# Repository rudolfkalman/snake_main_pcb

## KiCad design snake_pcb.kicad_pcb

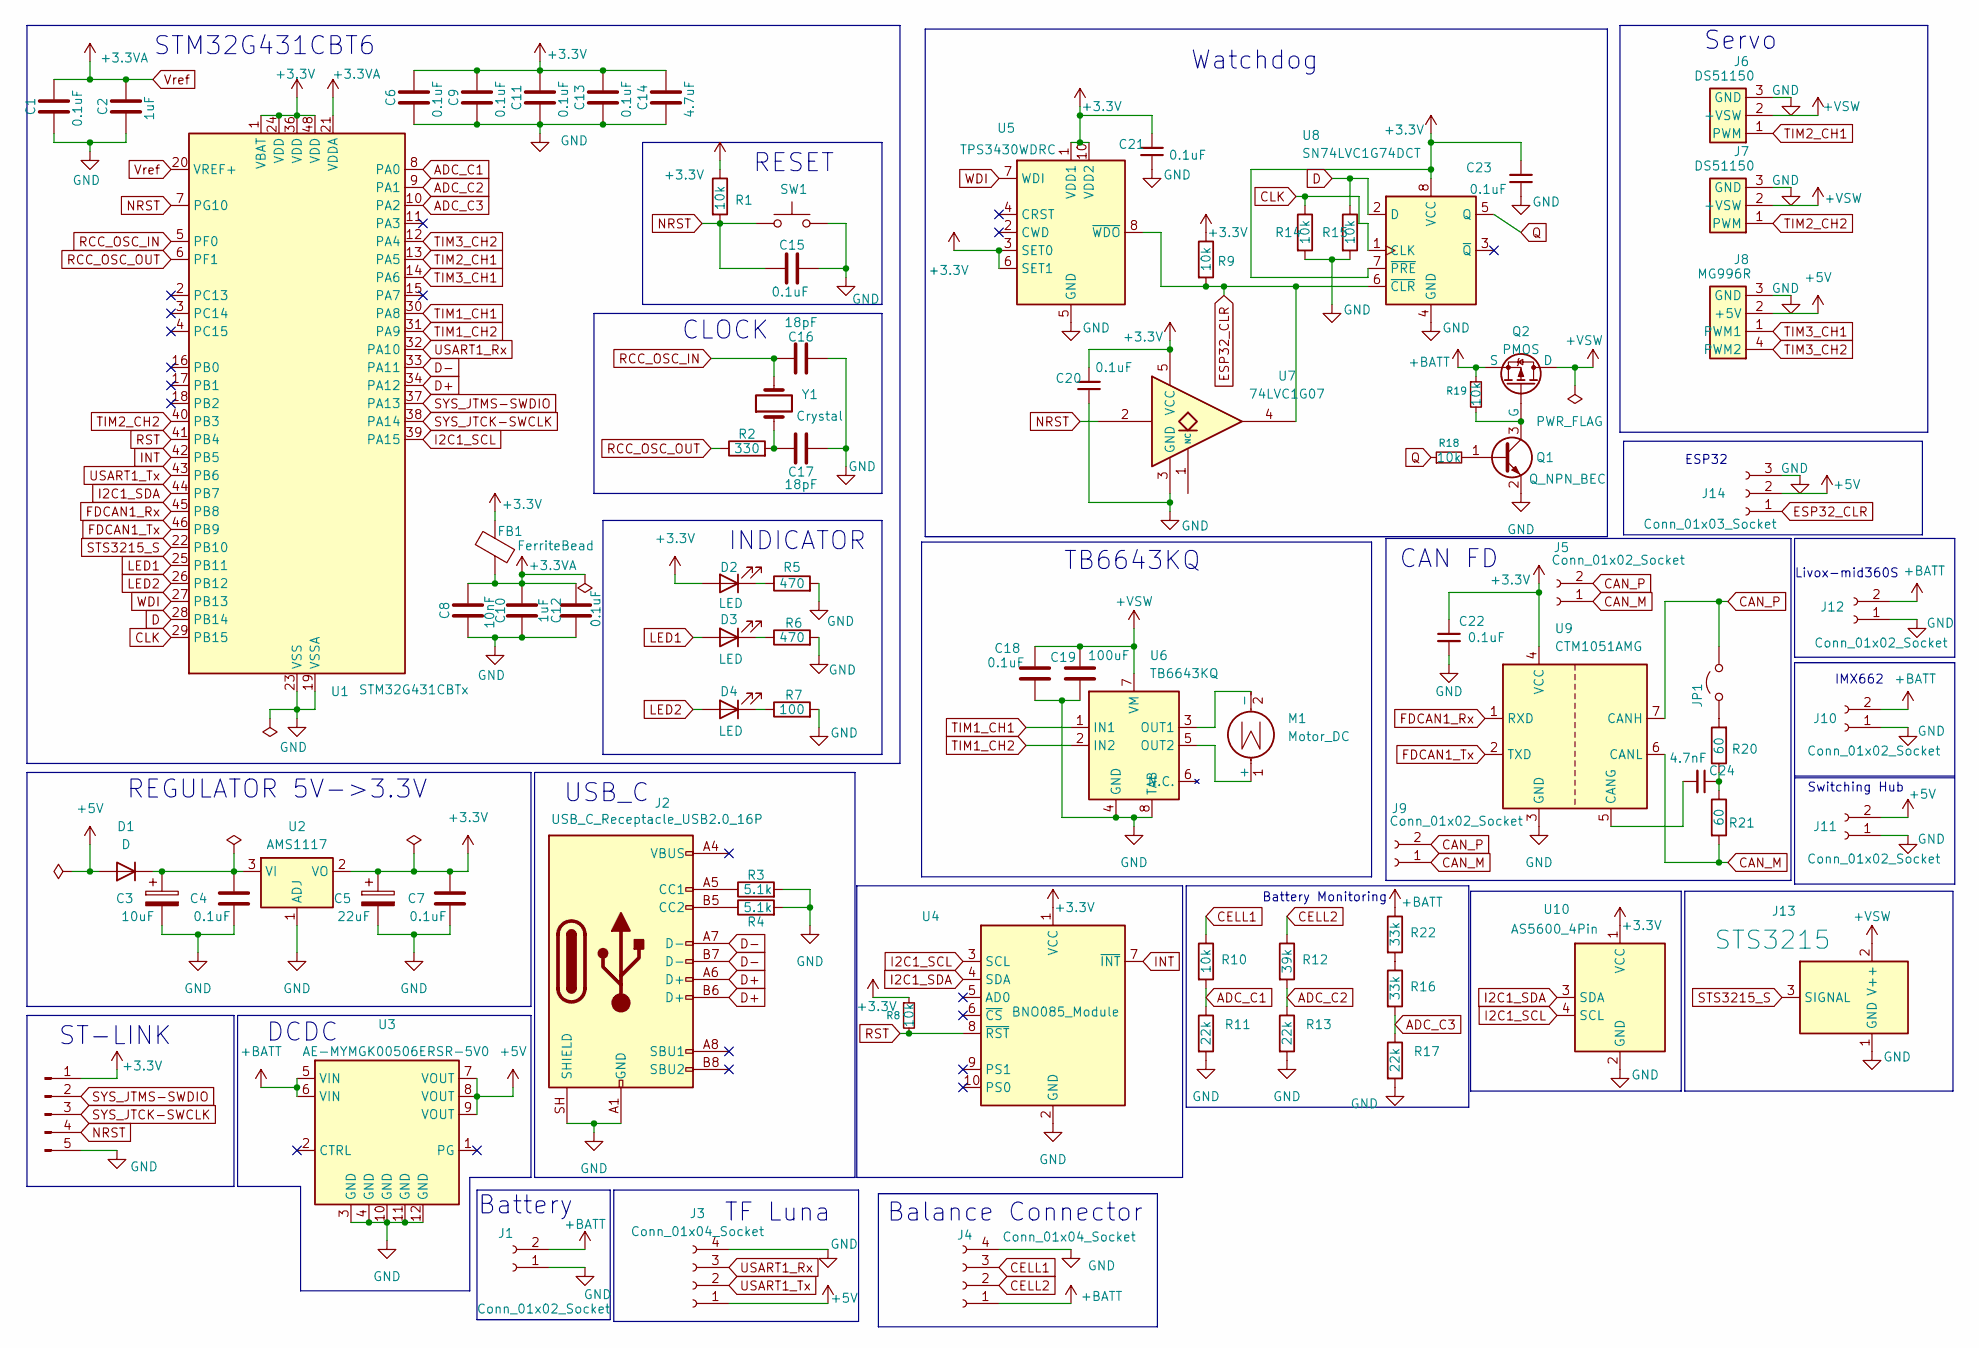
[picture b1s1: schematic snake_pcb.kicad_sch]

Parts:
C1, C4, C6, C7, C9, C11, C12, C13, C15, C18, C20, C21, C22, C23: 0.1uF; C_0603_1608Metric
C2, C10: 1uF; C_0603_1608Metric
C3: 10uF; C_CASE-A-3216-18(mm)
C5: 22uF; C_CASE-A-3216-18(mm)
C8: 10nF; C_0603_1608Metric
C14: 4.7uF; C_0603_1608Metric
C16, C17: 18pF; C_0603_1608Metric
C19: 100uF; C_Elec_6.3x7.7
C24: 4.7nF; C_0603_1608Metric
D1: D; D_DO-214AC(SMA)
D2, D3, D4: LED; LED_0603_1608Metric
FB1: FerriteBead; L_0603_1608Metric
J1: Conn_01x02_Socket; AMASS_XT30PW-M_1x02_P2.50mm_Horizontal
J2: USB_C_Receptacle_USB2.0_16P; USB_C_Receptacle_GCT_USB4110
J3: Conn_01x04_Socket; PinHeader_1x04_P2.54mm_Vertical
J4: Conn_01x04_Socket; JST_XH_B4B-XH-A_1x04_P2.50mm_Vertical
J5: Conn_01x02_Socket; JST_XH_S2B-XH-A_1x02_P2.50mm_Horizontal
J6, J7: DS51150; Servo_3Wire_3x6mm_P5mm
J8: MG996R; Servo_4Wire_3x6mm_P5mm
J9, J11: Conn_01x02_Socket; JST_XH_B2B-XH-A_1x02_P2.50mm_Vertical
J10: Conn_01x02_Socket; JST_PH_B2B-PH-K_1x02_P2.00mm_Vertical
J12: Conn_01x02_Socket; AMASS_XT30PW-F_1x02_P2.50mm_Horizontal
J13: STS3215; Molex_SPOX_5267-03A_1x03_P2.50mm_Vertical
J14: Conn_01x03_Socket; PinHeader_1x03_P2.54mm_Vertical
JP1: Jumper_2_Open; R_0603_1608Metric
M1: Motor_DC; AMASS_XT30PW-F_1x02_P2.50mm_Horizontal
Q1: Q_NPN_BEC; SOT-23
Q2: PMOS; TO-252-2_TabPin1
R1, R8, R9, R10, R14, R15, R18, R19: 10k; R_0603_1608Metric
R2: 330; R_0603_1608Metric
R3, R4: 5.1k; R_0603_1608Metric
R5, R6: 470; R_0603_1608Metric
R7: 100; R_0603_1608Metric
R11, R13, R17: 22k; R_0603_1608Metric
R12: 39k; R_0805_2012Metric
R16, R22: 33k; R_0603_1608Metric
R20, R21: 60; R_0603_1608Metric
ST-LINK1: Conn_01x05_Pin; PinHeader_1x05_P2.54mm_Vertical
SW1: SW_Push; SW_Tactile_SPST_NO_Straight_CK_PTS636Sx25SMTRLFS
U1: STM32G431CBTx; LQFP-48_7x7mm_P0.5mm
U2: AMS1117; SOT-223-3_TabPin2
U3: AE-MYMGK00506ERSR-5V0
U4: BNO085_Module; BNO085_Module_25.8x15.5mm_1x10_P2.54mm
U5: TPS3430WDRC; VSON-10-1EP_3x3mm_P0.5mm_EP1.65x2.4mm
U6: TB6643KQ; TB6643KQ_HSIP7_PCBHeatsink
U7: 74LVC1G07; SOT-353_SC-70-5
U8: SN74LVC1G74DCT; SSOP-8_2.95x2.8mm_P0.65mm
U9: CTM1051AMG; ZLG_CTM1051AMG_12.8x10.2mm_P2.54mm
U10: AS5600_4Pin; PinHeader_1x04_P2.54mm_Vertical
Y1: Crystal; Crystal_SMD_3225-4Pin_3.2x2.5mm

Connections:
+3.3V: C5.1, C6.2, C7.1, C9.2, C11.2, C13.2, C14.2, C20.1, C21.1, C22.1, C23.1, D2.2 (A), FB1.1, R1.1, R8.1, R9.1, ST-LINK1.1, U1.1 (VBAT), U1.24 (VDD), U1.36 (VDD), U1.48 (VDD), U2.2 (VO), U4.1 (VCC), U5.1 (VDD1), U5.3 (SET0), U5.6 (SET1), U5.10 (VDD2), U7.5 (VCC), U8.7 (~PRE), U8.8 (VCC), U9.4 (VCC), U10.1 (VCC)
+5V: D1.2 (A), J3.1, J8.2 (+5V), J11.2, J14.2, U3.7 (VOUT), U3.8 (VOUT), U3.9 (VOUT)
+BATT: J1.2, J4.1, J10.2, J12.2, Q2.3 (S), R19.1, R22.1, U3.5 (VIN), U3.6 (VIN)
+VSW: C18.1, C19.1, J6.2 (+VSW), J7.2 (+VSW), J13.2 (V++), Q2.1 (D), U6.7 (VM)
ADC_C1: R10.2, R11.1, U1.8 (PA0)
ADC_C2: R12.2, R13.1, U1.9 (PA1)
ADC_C3: R16.2, R17.1, U1.10 (PA2)
CAN_M: J5.1, J9.1, R21.2, U9.6 (CANL)
CAN_P: J5.2, J9.2, JP1.2 (B), U9.7 (CANH)
CELL1: J4.3, R10.1
CELL2: J4.2, R12.1
CLK: R14.1, U1.29 (PB15), U8.1 (CLK)
D: R15.1, U1.28 (PB14), U8.2 (D)
D+: J2.A6 (D+), J2.B6 (D+), U1.34 (PA12)
D-: J2.A7 (D-), J2.B7 (D-), U1.33 (PA11)
ESP32_CLR: J14.1, R9.2, U5.8 (~WDO), U7.4, U8.6 (~CLR)
FDCAN1_Rx: U1.45 (PB8), U9.1 (RXD)
FDCAN1_Tx: U1.46 (PB9), U9.2 (TXD)
GND: C1.1, C2.1, C3.2, C4.2, C5.2, C6.1, C7.2, C8.1, C9.1, C10.1, C11.1, C12.1, C13.1, C14.1, C15.2, C16.2, C17.1, C18.2, C19.2, C20.2, C21.2, C22.2, C23.2, J1.1, J2.A1 (GND), J2.A12 (GND), J2.B1 (GND), J2.B12 (GND), J2.SH (SHIELD), J3.4, J4.4, J6.3 (GND), J7.3 (GND), J8.3 (GND), J10.1, J11.1, J12.1, J13.1 (GND), J14.3, Q1.2 (E), R3.2, R4.2, R5.2, R6.2, R7.2, R11.2, R13.2, R14.2, R15.2, R17.2, ST-LINK1.5, SW1.2, U1.19 (VSSA), U1.23 (VSS), U1.35 (VSS), U1.47 (VSS), U2.1 (ADJ), U3.3 (GND), U3.4 (GND), U3.10 (GND), U3.11 (GND), U3.12 (GND), U4.2 (GND), U5.5 (GND), U5.11 (GND), U6.4 (GND), U6.8 (TAB), U7.3 (GND), U8.4 (GND), U9.3 (GND), U10.2 (GND)
I2C1_SCL: U1.39 (PA15), U4.3 (SCL), U10.4 (SCL)
I2C1_SDA: U1.44 (PB7), U4.4 (SDA), U10.3 (SDA)
INT: U1.42 (PB5), U4.7 (~INT)
LED1: D3.2 (A), U1.25 (PB11)
LED2: D4.2 (A), U1.26 (PB12)
NRST: C15.1, R1.2, ST-LINK1.4, SW1.1, U1.7 (PG10), U7.2
unnamed: C17.2, R2.2, Y1.1
unnamed: C24.1, R20.1, R21.1
unnamed: C3.1, C4.1, D1.1 (K), U2.3 (VI)
unnamed: D2.1 (K), R5.1
unnamed: D3.1 (K), R6.1
unnamed: D4.1 (K), R7.1
unnamed: J2.A5 (CC1), R3.1
unnamed: J2.B5 (CC2), R4.1
unnamed: JP1.1 (A), R20.2
unnamed: M1.1 (+), U6.5 (OUT2)
unnamed: M1.2 (-), U6.3 (OUT1)
unnamed: Q1.1 (B), R18.2
unnamed: Q1.3 (C), Q2.2 (G), R19.2
unnamed: R16.1, R22.2
unnamed: C24.2, U9.5 (CANG)
Q: R18.1, U8.5 (Q)
RCC_OSC_IN: C16.1, U1.5 (PF0), Y1.2
RCC_OSC_OUT: R2.1, U1.6 (PF1)
RST: R8.2, U1.41 (PB4), U4.8 (~RST)
STS3215_S: J13.3 (SIGNAL), U1.22 (PB10)
SYS_JTCK-SWCLK: ST-LINK1.3, U1.38 (PA14)
SYS_JTMS-SWDIO: ST-LINK1.2, U1.37 (PA13)
TIM1_CH1: U1.30 (PA8), U6.1 (IN1)
TIM1_CH2: U1.31 (PA9), U6.2 (IN2)
TIM2_CH1: J6.1 (PWM), U1.13 (PA5)
TIM2_CH2: J7.1 (PWM), U1.40 (PB3)
TIM3_CH1: J8.1 (PWM1), U1.14 (PA6)
TIM3_CH2: J8.4 (PWM2), U1.12 (PA4)
USART1_Rx: J3.3, U1.32 (PA10)
USART1_Tx: J3.2, U1.43 (PB6)
Vref: C1.2, C2.2, C8.2, C10.2, C12.2, FB1.2, U1.20 (VREF+), U1.21 (VDDA)
WDI: U1.27 (PB13), U5.7 (WDI)

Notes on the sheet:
STM32G431CBT6
INDICATOR
DCDC
Battery
Battery Monitoring
CAN FD
ST-LINK
USB_C
Balance Connector
Livox-mid360S
REGULATOR 5V->3.3V
TF Luna
Servo
Switching Hub
CLOCK
TB6643KQ
ESP32
IMX662
RESET
Watchdog

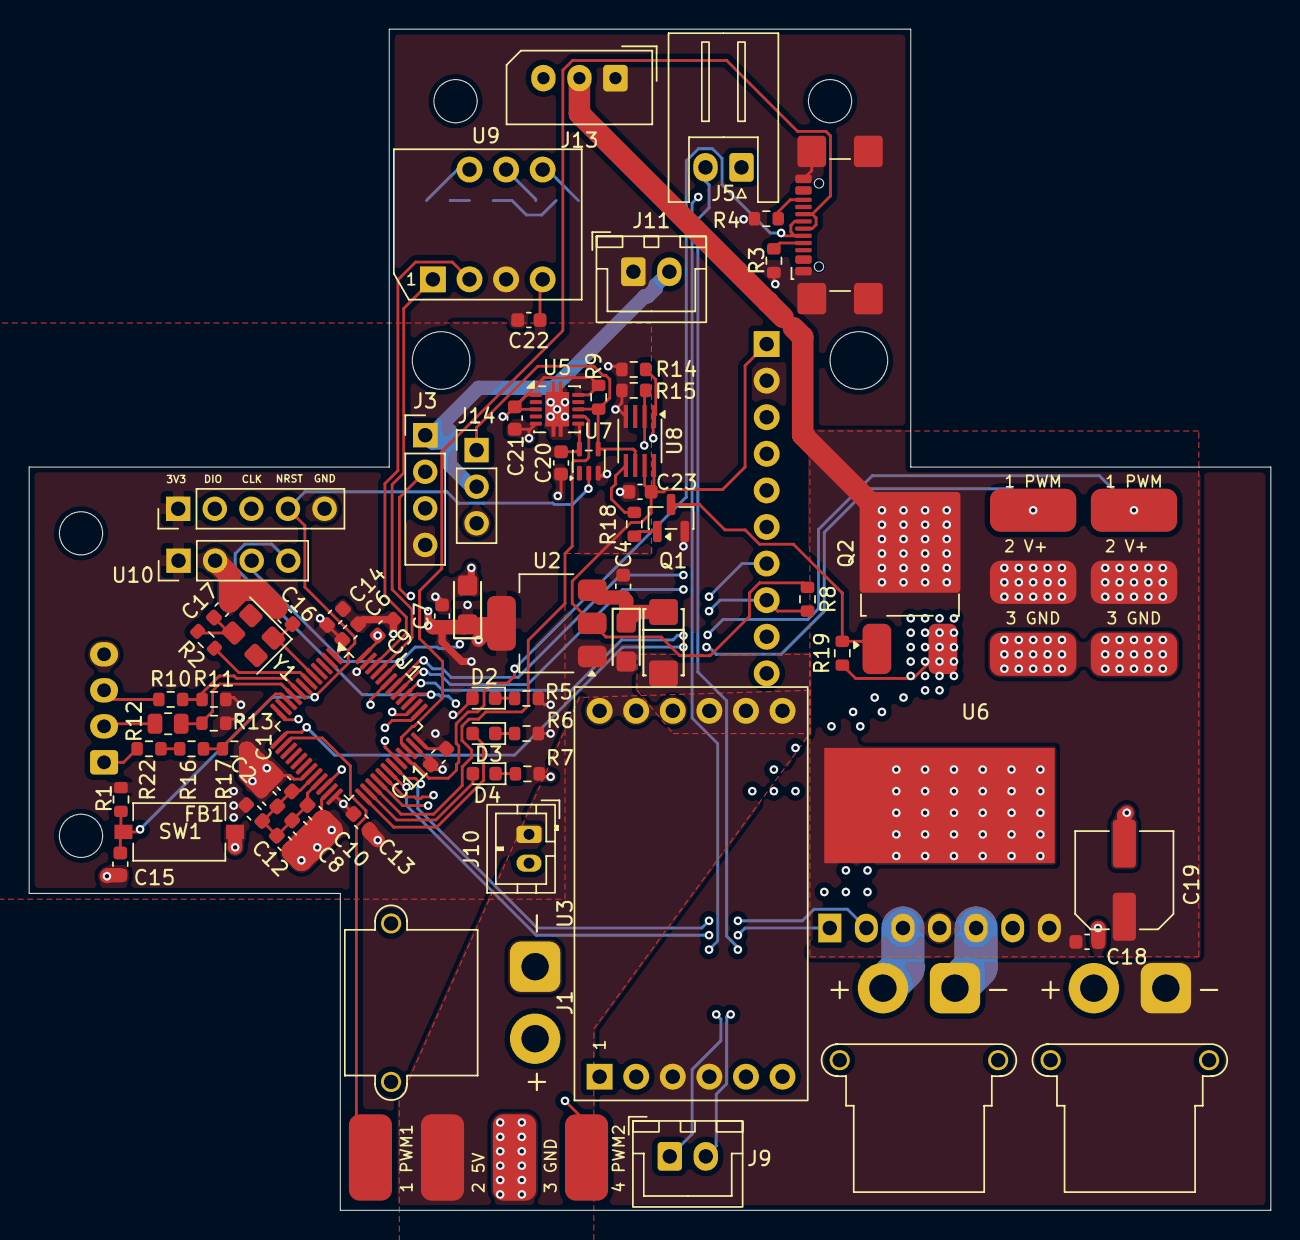
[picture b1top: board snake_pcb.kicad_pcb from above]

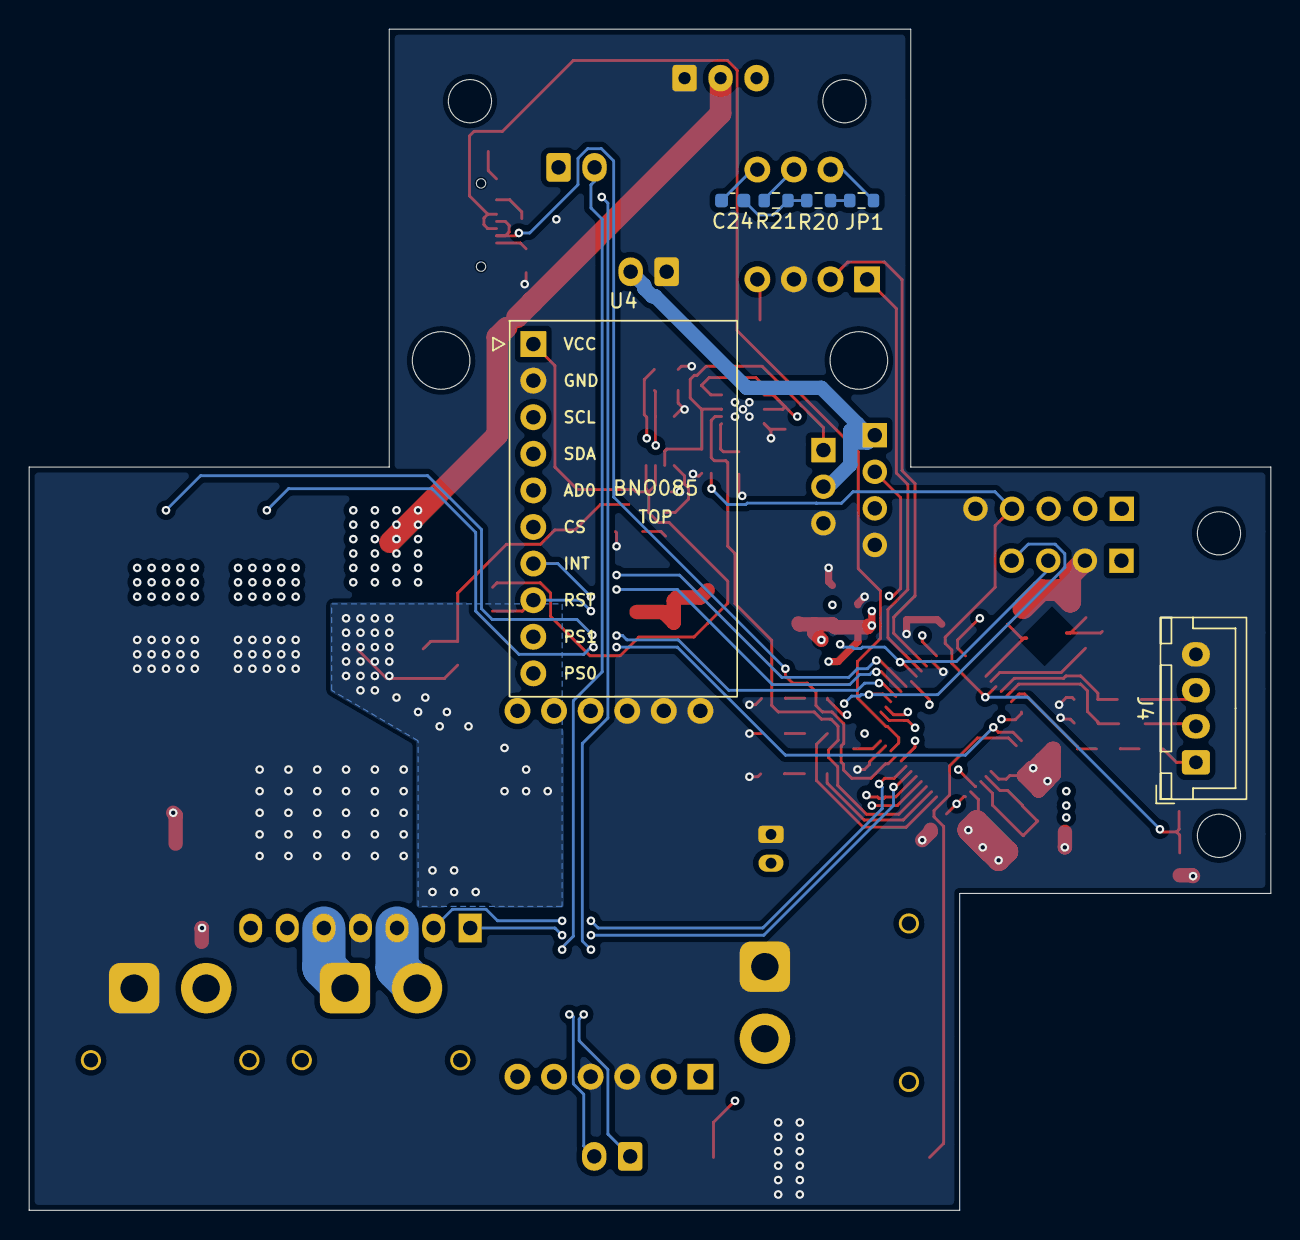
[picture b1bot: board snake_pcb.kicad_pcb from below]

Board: 4 copper layers, 86.2 x 82.0 mm, 82 parts (6 on the bottom side), 57 nets.

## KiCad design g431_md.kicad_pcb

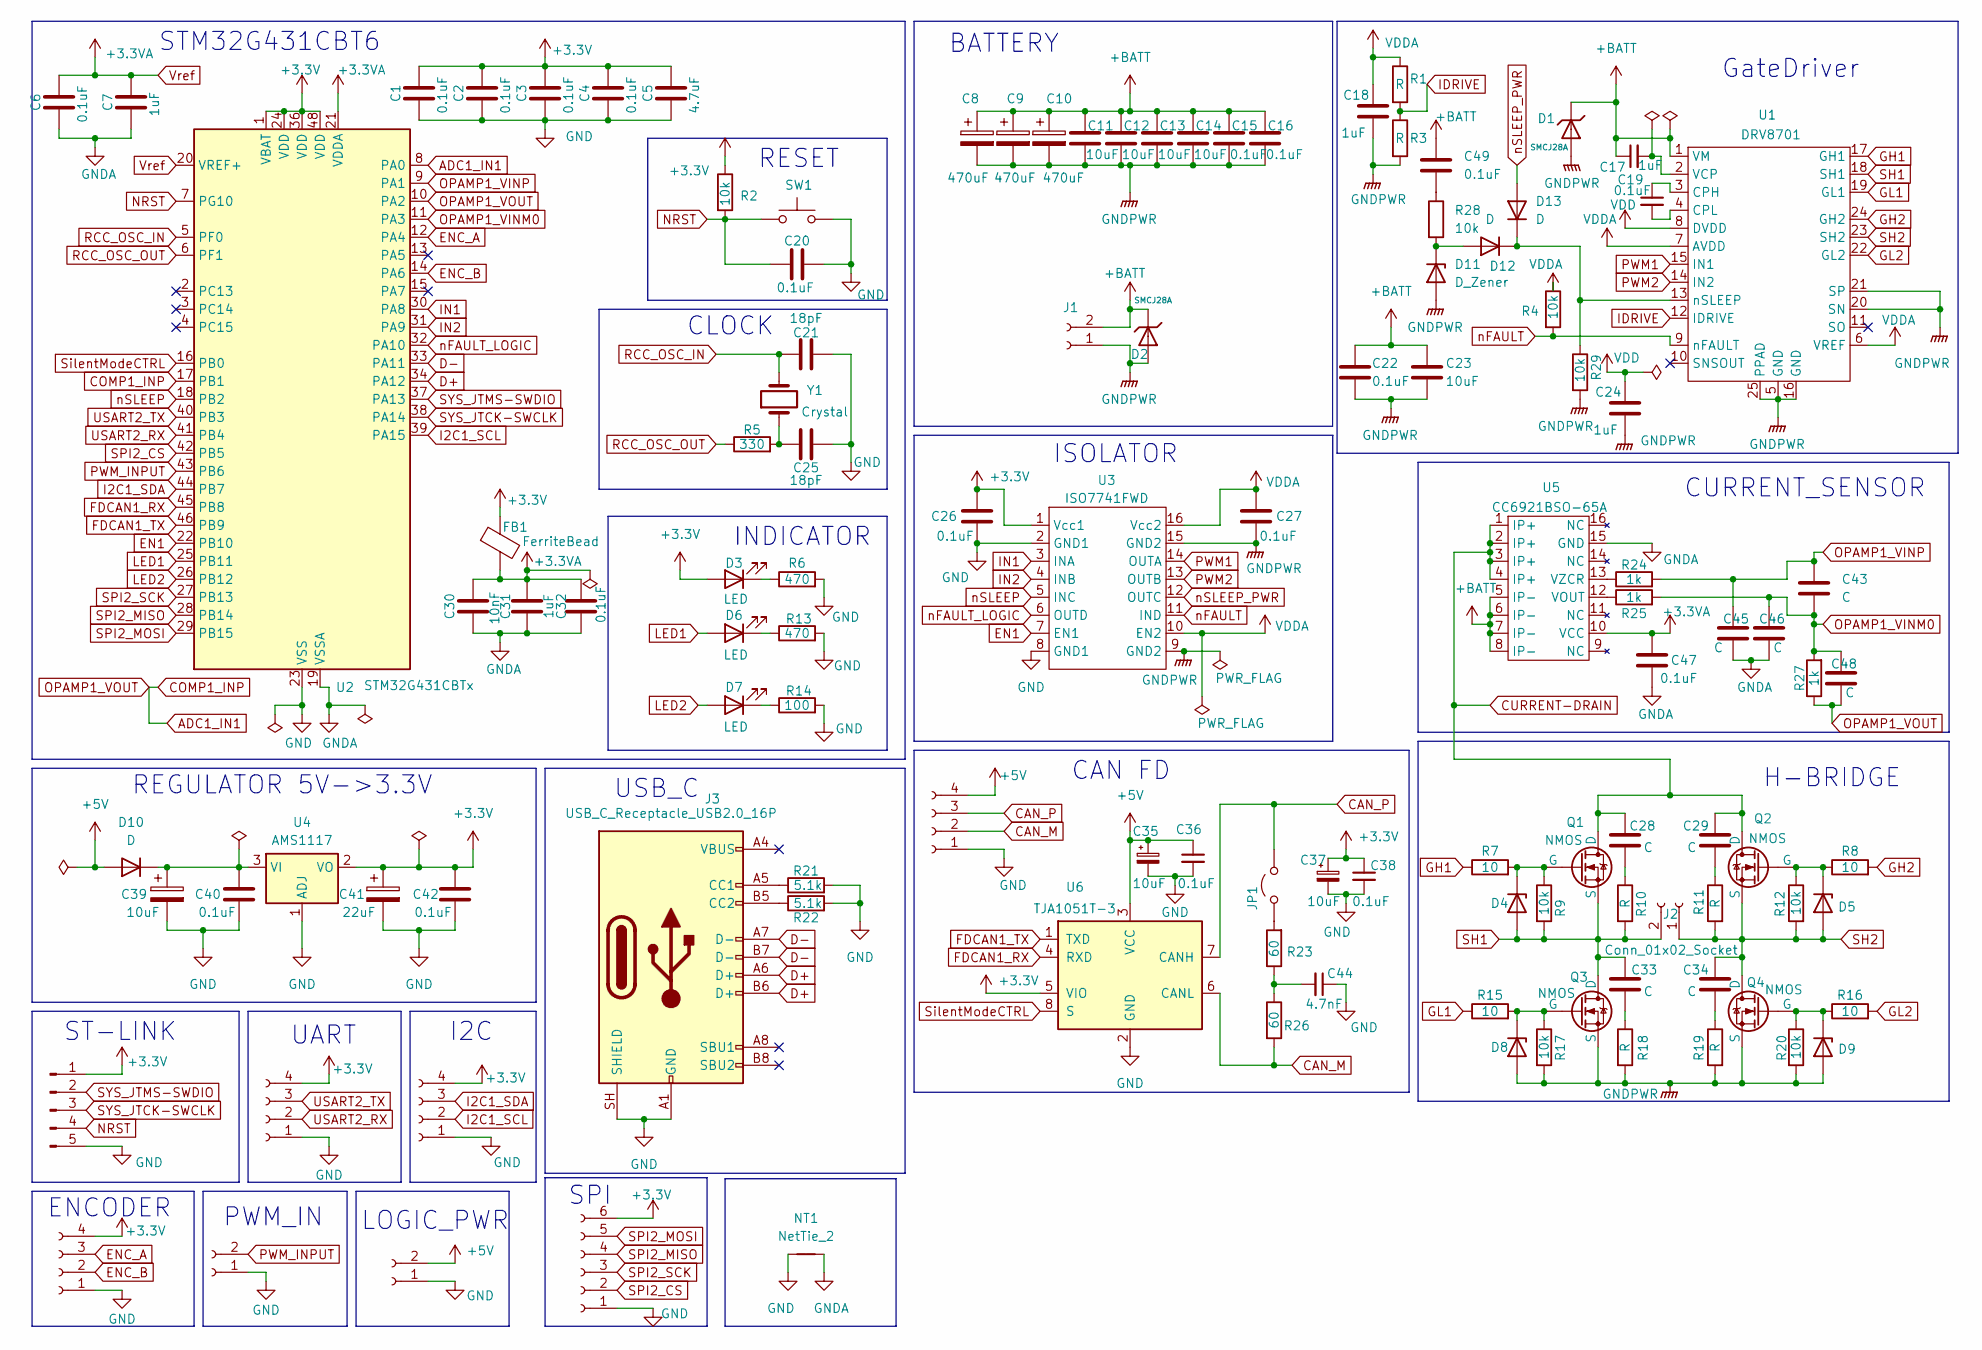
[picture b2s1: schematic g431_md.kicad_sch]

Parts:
C1, C2, C3, C4, C6, C15, C16, C19, C20, C22, C26, C27, C32, C36, C38, C40, C42, C47, C49: 0.1uF; C_0603_1608Metric
C5: 4.7uF; C_0603_1608Metric
C7, C17, C18, C24, C31: 1uF; C_0603_1608Metric
C8, C9, C10: 470uF; CP_Radial_D10.0mm_P5.00mm
C11, C12, C13, C14, C23, C35, C37: 10uF; C_0603_1608Metric
C21, C25: 18pF; C_0603_1608Metric
C28, C29, C33, C34: C; C_0805_2012Metric
C30: 10nF; C_0603_1608Metric
C39: 10uF; C_CASE-A-3216-18(mm)
C41: 22uF; C_CASE-A-3216-18(mm)
C43, C45, C46, C48: C; C_0603_1608Metric
C44: 4.7nF; C_0603_1608Metric
CAN1: Conn_01x04_Socket; JST_XH_S4B-XH-A_1x04_P2.50mm_Horizontal
D1, D2: SMCJ28A; D_SMC; Clamping Voltage 45.4V; Voltage - Breakdown 34.4V; Part SMCJ28A; LCSC C42371538
D3, D6, D7: LED; LED_0603_1608Metric
D4, D5, D8, D9: D_Zener; D_SOD-123
D10: D; D_DO-214AC(SMA)
D11: D_Zener; D_SOD-323F
D12, D13: D; Nexperia_CFP3_SOD-123W
ENCODER1: Conn_01x04_Socket; JST_XH_S4B-XH-A_1x04_P2.50mm_Horizontal
FB1: FerriteBead; L_0603_1608Metric
I2C1: Conn_01x04_Socket; JST_XH_S4B-XH-A_1x04_P2.50mm_Horizontal
J1, J2: Conn_01x02_Socket; AMASS_XT60PW-M_1x02_P7.20mm_Horizontal
J3: USB_C_Receptacle_USB2.0_16P; USB_C_Receptacle_GCT_USB4110
JP1: Jumper_2_Open; PinHeader_1x03_P2.54mm_Vertical
NT1: NetTie_2; NetTie-2_SMD_Pad0.5mm
PWM1: Conn_01x02_Socket; JST_XH_S2B-XH-A_1x02_P2.50mm_Horizontal
PWR1: Conn_01x02_Socket; JST_XH_S2B-XH-A_1x02_P2.50mm_Horizontal
Q1, Q2, Q3, Q4: NMOS; TO-263-2
R1, R3: R; R_0603_1608Metric
R2, R4, R9, R12, R17, R20, R28, R29: 10k; R_0603_1608Metric
R5: 330; R_0603_1608Metric
R6, R13: 470; R_0603_1608Metric
R7, R8, R15, R16: 10; R_0603_1608Metric
R10, R11, R18, R19: R; R_0805_2012Metric
R14: 100; R_0603_1608Metric
R21, R22: 5.1k; R_0603_1608Metric
R23, R26: 60; R_0603_1608Metric
R24, R25, R27: 1k; R_0603_1608Metric
SPI1: Conn_01x06_Socket; JST_XH_S6B-XH-A_1x06_P2.50mm_Horizontal
ST-LINK1: Conn_01x05_Pin; PinHeader_1x05_P2.54mm_Vertical
SW1: SW_Push; SW_Tactile_SPST_NO_Straight_CK_PTS636Sx25SMTRLFS
U1: DRV8701; Texas_RGE0024H_VQFN-24-1EP_4x4mm_P0.5mm_EP2.7x2.7mm_Thermal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
U2: STM32G431CBTx; LQFP-48_7x7mm_P0.5mm
U3: ISO7741FWD; SOIC-16W_7.5x10.3mm_P1.27mm
U4: AMS1117; SOT-223-3_TabPin2
U5: CC6921BSO-65A; SOIC-16W_7.5x10.3mm_P1.27mm
U6: TJA1051T-3; SOIC-8_3.9x4.9mm_P1.27mm
UART1: Conn_01x04_Socket; JST_XH_S4B-XH-A_1x04_P2.50mm_Horizontal
Y1: Crystal; Crystal_SMD_3225-4Pin_3.2x2.5mm

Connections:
+3.3V: C1.2, C2.2, C3.2, C4.2, C5.2, C26.1, C37.1, C38.1, C41.1, C42.1, D3.2 (A), ENCODER1.4, FB1.1, I2C1.4, R2.1, SPI1.6, ST-LINK1.1, U2.1 (VBAT), U2.24 (VDD), U2.36 (VDD), U2.48 (VDD), U3.1 (Vcc1), U4.2 (VO), U6.5 (VIO), UART1.4
+5V: C35.1, C36.1, CAN1.4, D10.2 (A), PWR1.2, U6.3 (VCC)
+BATT: C8.1, C9.1, C10.1, C11.1, C12.1, C13.1, C14.1, C15.1, C16.1, C17.1, C22.1, C23.1, C49.1, D1.1, D2.1, J1.2, U1.1 (VM), U5.5 (IP-), U5.6 (IP-), U5.7 (IP-), U5.8 (IP-)
ADC1_IN1: C48.2, R27.1, U2.8 (PA0), U2.10 (PA2), U2.17 (PB1)
CAN_M: CAN1.2, R26.2, U6.6 (CANL)
CAN_P: CAN1.3, JP1.2 (B), U6.7 (CANH)
CURRENT-DRAIN: C28.1, C29.1, Q1.2 (D), Q2.2 (D), U5.1 (IP+), U5.2 (IP+), U5.3 (IP+), U5.4 (IP+)
D+: J3.A6 (D+), J3.B6 (D+), U2.34 (PA12)
D-: J3.A7 (D-), J3.B7 (D-), U2.33 (PA11)
EN1: U2.22 (PB10), U3.7 (EN1)
ENC_A: ENCODER1.3, U2.12 (PA4)
ENC_B: ENCODER1.2, U2.14 (PA6)
FDCAN1_RX: U2.45 (PB8), U6.4 (RXD)
FDCAN1_TX: U2.46 (PB9), U6.1 (TXD)
GH1: R7.1, U1.17 (GH1)
GH2: R8.2, U1.24 (GH2)
GL1: R15.1, U1.19 (GL1)
GL2: R16.2, U1.22 (GL2)
GND: C1.1, C2.1, C3.1, C4.1, C5.1, C20.2, C21.2, C25.1, C26.2, C35.2, C36.2, C37.2, C38.2, C39.2, C40.2, C41.2, C42.2, C44.1, CAN1.1, ENCODER1.1, I2C1.1, J3.A1 (GND), J3.A12 (GND), J3.B1 (GND), J3.B12 (GND), J3.SH (SHIELD), NT1.1, PWM1.1, PWR1.1, R6.2, R13.2, R14.2, R21.2, R22.2, SPI1.1, ST-LINK1.5, SW1.2, U2.23 (VSS), U2.35 (VSS), U2.47 (VSS), U3.2 (GND1), U3.8 (GND1), U4.1 (ADJ), U6.2 (GND), UART1.1
GNDA: C6.1, C7.1, C30.1, C31.1, C32.1, C45.2, C46.2, C47.2, NT1.2, U2.19 (VSSA), U5.15 (GND)
GNDPWR: C8.2, C9.2, C10.2, C11.2, C12.2, C13.2, C14.2, C15.2, C16.2, C18.2, C22.2, C23.2, C24.2, C27.2, D1.2, D2.2, D8.2 (A), D9.2 (A), D11.2 (A), J1.1, Q3.3 (S), Q4.3 (S), R3.2, R17.2, R18.2, R19.2, R20.2, R29.2, U1.5 (GND), U1.16 (GND), U1.20 (SN), U1.21 (SP), U1.25 (PPAD), U3.9 (GND2), U3.15 (GND2)
I2C1_SCL: I2C1.2, U2.39 (PA15)
I2C1_SDA: I2C1.3, U2.44 (PB7)
IDRIVE: R1.2, R3.1, U1.12 (IDRIVE)
IN1: U2.30 (PA8), U3.3 (INA)
IN2: U2.31 (PA9), U3.4 (INB)
LED1: D6.2 (A), U2.25 (PB11)
LED2: D7.2 (A), U2.26 (PB12)
NRST: C20.1, R2.2, ST-LINK1.4, SW1.1, U2.7 (PG10)
unnamed: C25.2, R5.2, Y1.1
unnamed: C28.2, R10.1
unnamed: C29.2, R11.1
unnamed: C33.2, R18.1
unnamed: C34.2, R19.1
unnamed: C44.2, R23.1, R26.1
unnamed: C49.2, R28.1
unnamed: D3.1 (K), R6.1
unnamed: D4.1 (K), Q1.1 (G), R7.2, R9.1
unnamed: D5.1 (K), Q2.1 (G), R8.1, R12.1
unnamed: D6.1 (K), R13.1
unnamed: D7.1 (K), R14.1
unnamed: D8.1 (K), Q3.1 (G), R15.2, R17.1
unnamed: D9.1 (K), Q4.1 (G), R16.1, R20.1
unnamed: C39.1, C40.1, D10.1 (K), U4.3 (VI)
unnamed: D11.1 (K), D12.2 (A), R28.2
unnamed: D12.1 (K), D13.1 (K), R29.1, U1.13 (nSLEEP)
unnamed: J3.A5 (CC1), R21.1
unnamed: J3.B5 (CC2), R22.1
unnamed: JP1.1 (A), R23.2
unnamed: C19.1, U1.3 (CPH)
unnamed: C19.2, U1.4 (CPL)
unnamed: C17.2, U1.2 (VCP)
unnamed: R25.1, U5.12 (VOUT)
unnamed: R24.1, U5.13 (VZCR)
OPAMP1_VINM0: C43.2, C46.1, C48.1, R25.2, R27.2, U2.11 (PA3)
OPAMP1_VINP: C43.1, C45.1, R24.2, U2.9 (PA1)
PWM1: U1.15 (IN1), U3.14 (OUTA)
PWM2: U1.14 (IN2), U3.13 (OUTB)
PWM_INPUT: PWM1.2, U2.43 (PB6)
RCC_OSC_IN: C21.1, U2.5 (PF0), Y1.2
RCC_OSC_OUT: R5.1, U2.6 (PF1)
SH1: C33.1, D4.2 (A), J2.2, Q1.3 (S), Q3.2 (D), R9.2, R10.2, U1.18 (SH1)
SH2: C34.1, D5.2 (A), J2.1, Q2.3 (S), Q4.2 (D), R11.2, R12.2, U1.23 (SH2)
SPI2_CS: SPI1.2, U2.42 (PB5)
SPI2_MISO: SPI1.4, U2.28 (PB14)
SPI2_MOSI: SPI1.5, U2.29 (PB15)
SPI2_SCK: SPI1.3, U2.27 (PB13)
SYS_JTCK-SWCLK: ST-LINK1.3, U2.38 (PA14)
SYS_JTMS-SWDIO: ST-LINK1.2, U2.37 (PA13)
SilentModeCTRL: U2.16 (PB0), U6.8 (S)
USART2_RX: U2.41 (PB4), UART1.2
USART2_TX: U2.40 (PB3), UART1.3
VDD: C24.1, U1.8 (DVDD)
VDDA: C18.1, C27.1, R1.1, R4.1, U1.6 (VREF), U1.7 (AVDD), U3.10 (EN2), U3.16 (Vcc2)
Vref: C6.2, C7.2, C30.2, C31.2, C32.2, C47.1, FB1.2, U2.20 (VREF+), U2.21 (VDDA), U5.10 (VCC)
nFAULT: R4.2, U1.9 (nFAULT), U3.11 (IND)
nFAULT_LOGIC: U2.32 (PA10), U3.6 (OUTD)
nSLEEP: U2.18 (PB2), U3.5 (INC)
nSLEEP_PWR: D13.2 (A), U3.12 (OUTC)

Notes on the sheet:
STM32G431CBT6
UART
INDICATOR
ISOLATOR
H-BRIDGE
CAN FD
SPI
ST-LINK
USB_C
REGULATOR 5V->3.3V
CURRENT_SENSOR
BATTERY
ENCODER
CLOCK
LOGIC_PWR
PWM_IN
I2C
GateDriver
RESET

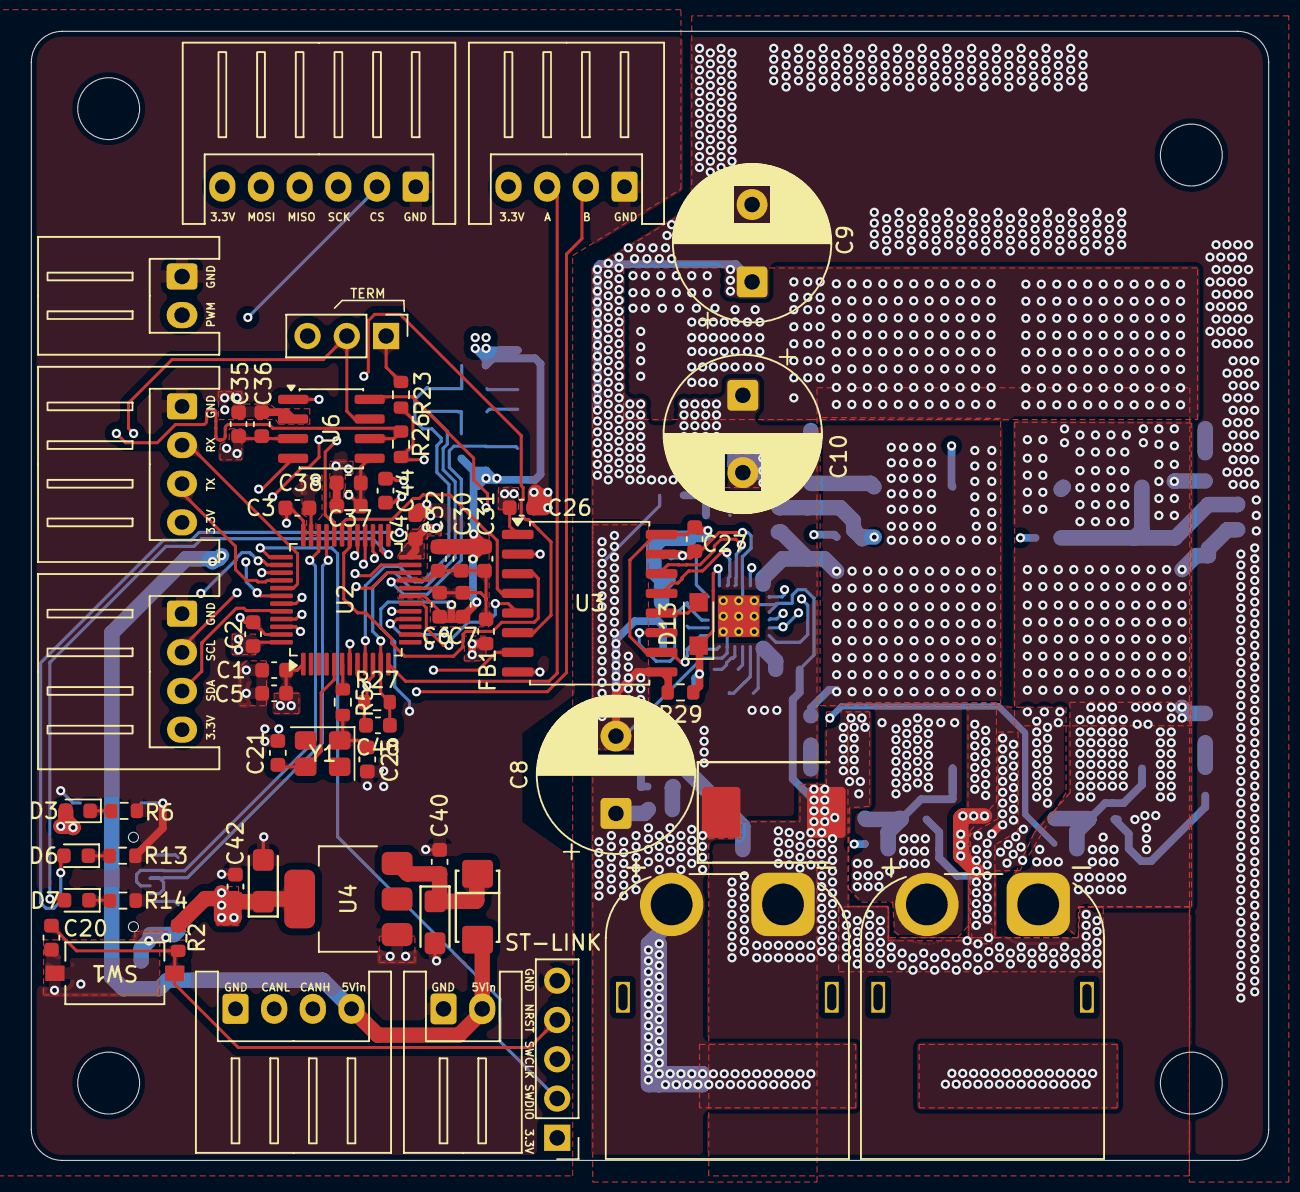
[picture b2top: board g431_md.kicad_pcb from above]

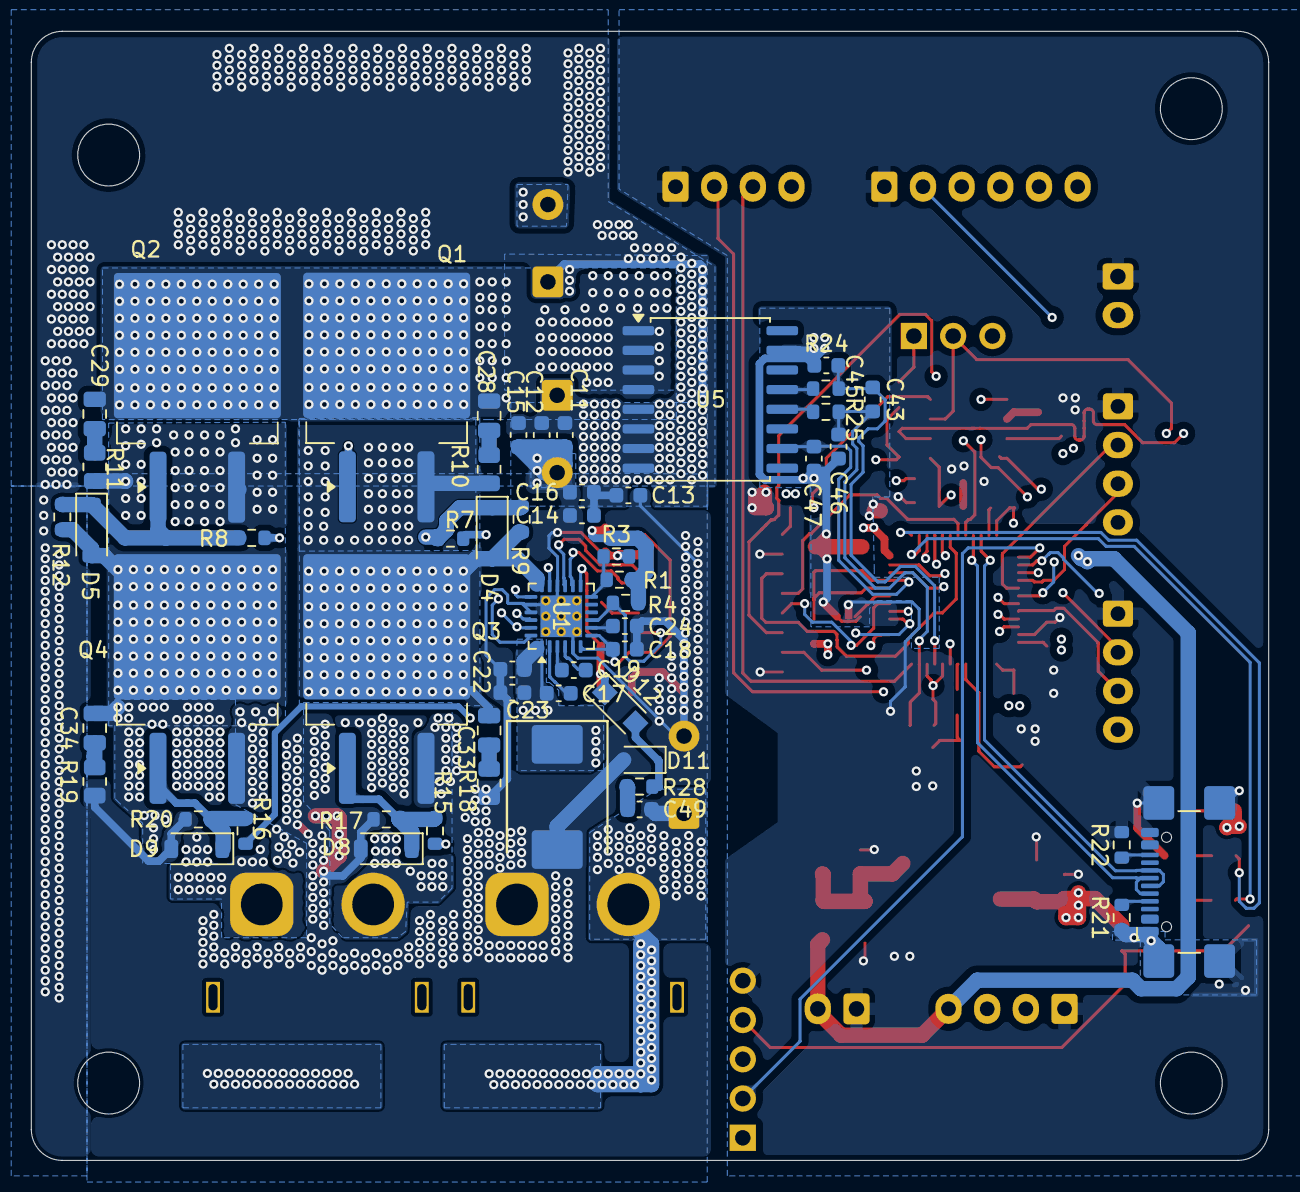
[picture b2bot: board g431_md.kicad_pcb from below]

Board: 4 copper layers, 80.0 x 73.0 mm, 117 parts (55 on the bottom side), 79 nets.

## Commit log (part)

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2026-04-08 Connected gnd to gnda
2026-05-06 fix power circuit starter
